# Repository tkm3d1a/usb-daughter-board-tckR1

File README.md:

# usb-daughter-board-tckR1
 USB Type-C Daughter Board - TKDesign - R1

Intent is to be a general purpose USB-C Daughter board, meant to break out the circuit onto a single board, meant for use in future KB design ideas.

All work will be done in KiCad as I learn it, this is meant to be the initial revision only, future revs will get new repos as major design shifts happen.

Initial idea is for SMT with production from a board manufacturer.  Break out will be done through a planned JST style connector. Breakout will be D+/D-/VCC/GND.

More info to be added through devolpment.

//////////UPDATE 1://///////////

Initial Prototype Board ordered for testing 1/31/2021

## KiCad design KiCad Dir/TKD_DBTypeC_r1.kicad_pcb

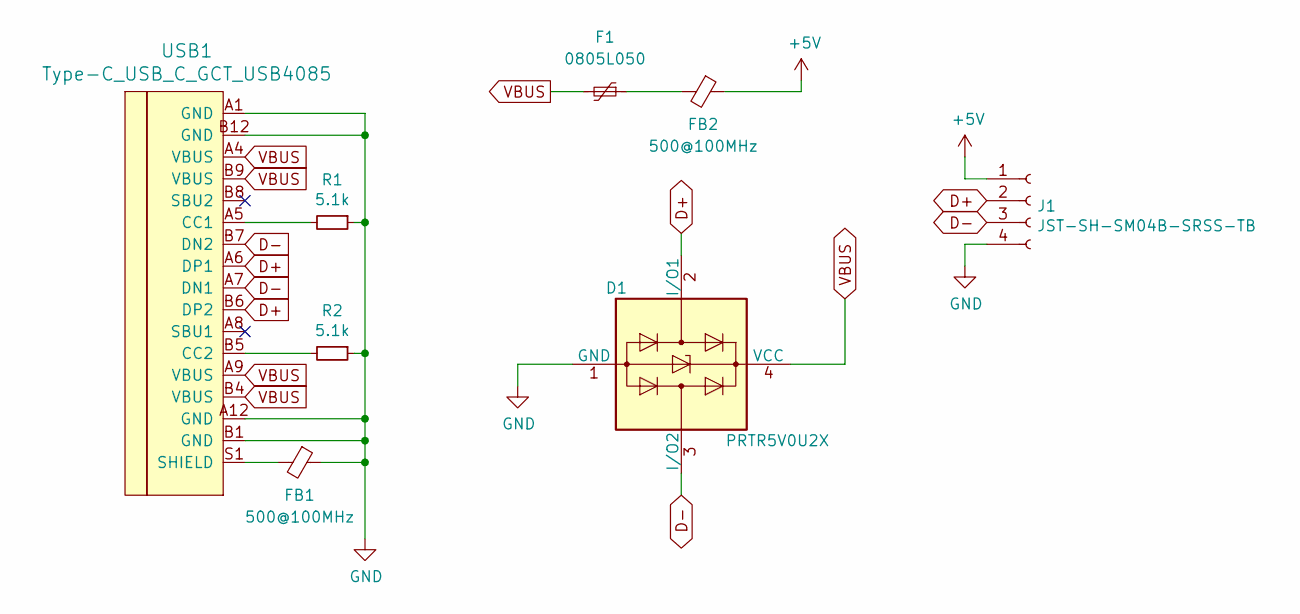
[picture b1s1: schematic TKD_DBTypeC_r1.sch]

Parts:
D1: PRTR5V0U2X; SOT-143
F1: 0805L050; Fuse_0805_2012Metric
FB1, FB2: 500@100MHz; L_0805_2012Metric
J1: JST-SH-SM04B-SRSS-TB; JST_SH_SM04B-SRSS-TB_1x04-1MP_P1.00mm_Horizontal
R1, R2: 5.1k; R_0805_2012Metric
USB1: Type-C_USB_C_GCT_USB4085; USB_C_Receptacle_GCT_USB4085

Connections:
+5V: FB2.1, J1.1
D+: D1.2 (I/O1), J1.2, USB1.A6 (DP1), USB1.B6 (DP2)
D-: D1.3 (I/O2), J1.3, USB1.A7 (DN1), USB1.B7 (DN2)
GND: D1.1 (GND), FB1.1, J1.4, R1.1, R2.1, USB1.A1 (GND), USB1.A12 (GND), USB1.B1 (GND), USB1.B12 (GND); also elsewhere on the board
unnamed: F1.1, FB2.2
unnamed: FB1.2, USB1.S1 (SHIELD)
unnamed: R1.2, USB1.A5 (CC1)
unnamed: R2.2, USB1.B5 (CC2)
VBUS: D1.4 (VCC), F1.2, USB1.A4 (VBUS), USB1.A9 (VBUS), USB1.B4 (VBUS), USB1.B9 (VBUS)

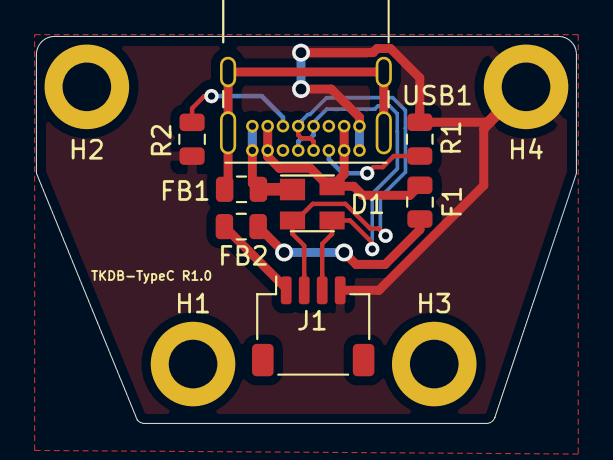
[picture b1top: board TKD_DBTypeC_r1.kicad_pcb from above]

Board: 2 copper layers, 30.0 x 21.5 mm, 12 parts (0 on the bottom side), 9 nets.

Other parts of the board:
H1, H2, H3: MountingHole; MountingHole_2.7mm_M2.5_DIN965_Pad
H4: MountingHole_Pad; MountingHole_2.7mm_M2.5_DIN965_Pad

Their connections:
GND: H4.1; also elsewhere on the board

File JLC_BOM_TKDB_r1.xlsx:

Comment | Designator | Footprint | LCSC Part #（optional）
500@100mhz | FB1,FB2 | 0805_I | C281168
500ma | F1 | 0805_Fuse | C261942
PRTR5V0U2X | D1 | SOT-143 | C12333
5.1kΩ | R1,R2 | 0805_R
JST 4pin | J1 | 1x04-1MP_P1.00mm_Horizontal | C160404

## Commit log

2021-01-12 some boardlayout work
2021-01-18 pcb/schemea update
2021-01-29 Edge cuts placed, r1 done
2021-01-29 gerber files - r1
2021-01-30 BOM generation - completed order #1
2021-02-01 Proto Ordered
